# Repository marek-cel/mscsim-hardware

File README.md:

# mscsim-hardware
Flight simulator hardware.

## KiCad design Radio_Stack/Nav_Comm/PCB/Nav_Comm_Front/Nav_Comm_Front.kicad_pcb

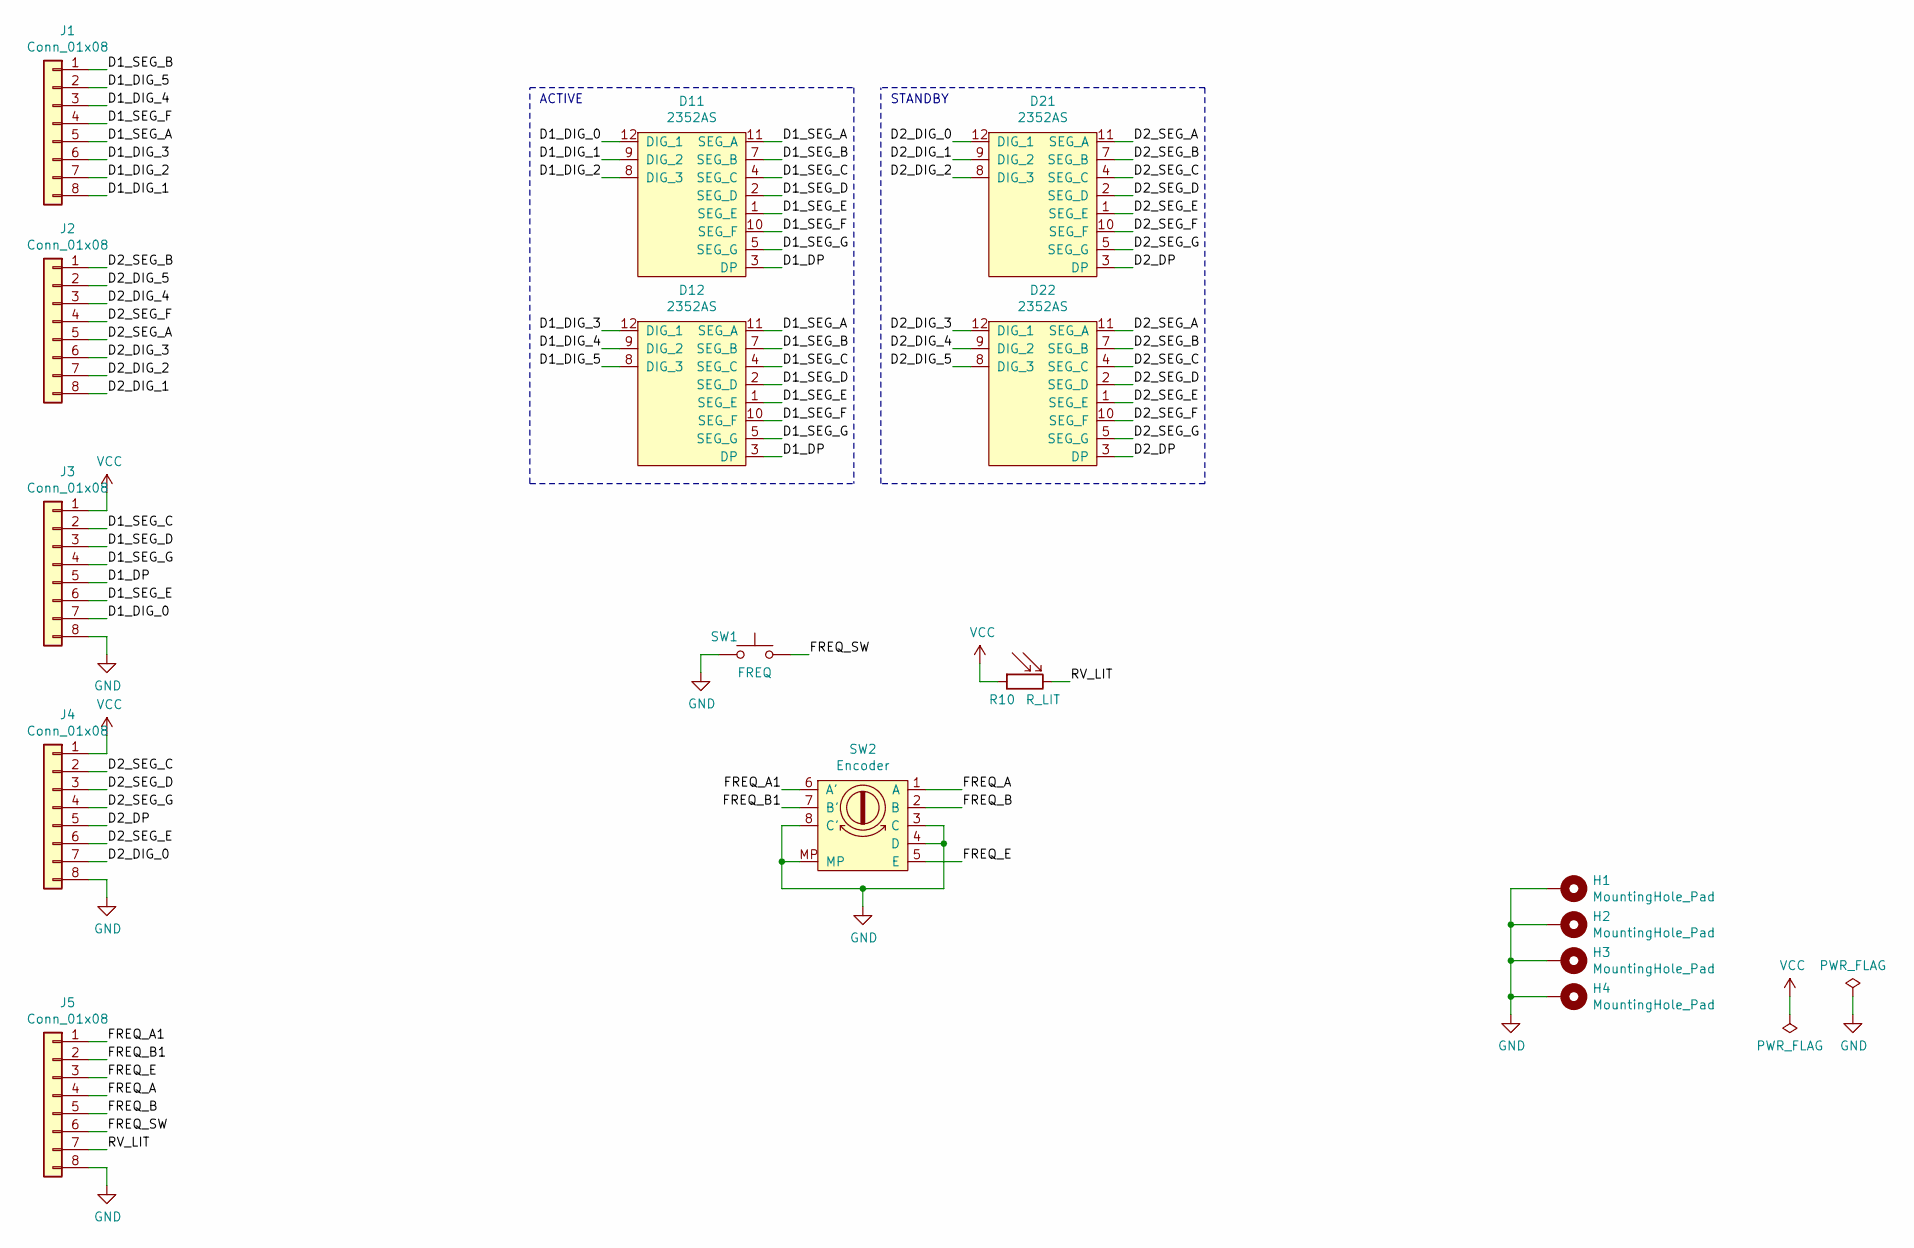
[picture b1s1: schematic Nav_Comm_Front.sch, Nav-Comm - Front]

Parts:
D11, D12, D21, D22: 2352AS
H1, H2, H3, H4: MountingHole_Pad; MountingHole_2.7mm_M2.5_Pad
J1, J2, J3, J4, J5: Conn_01x08; PinHeader_1x08_P2.54mm_Vertical
R10: R_LIT; GL55
SW1: FREQ; SW_PUSH_6mm
SW2: Encoder; EC11EBB24C03

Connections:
/D1_DIG_0: D11.12 (DIG_1), J3.7
/D1_DIG_1: D11.9 (DIG_2), J1.8
/D1_DIG_2: D11.8 (DIG_3), J1.7
/D1_DIG_3: D12.12 (DIG_1), J1.6
/D1_DIG_4: D12.9 (DIG_2), J1.3
/D1_DIG_5: D12.8 (DIG_3), J1.2
/D1_DP: D11.3 (DP), D12.3 (DP), J3.5
/D1_SEG_A: D11.11 (SEG_A), D12.11 (SEG_A), J1.5
/D1_SEG_B: D11.7 (SEG_B), D12.7 (SEG_B), J1.1
/D1_SEG_C: D11.4 (SEG_C), D12.4 (SEG_C), J3.2
/D1_SEG_D: D11.2 (SEG_D), D12.2 (SEG_D), J3.3
/D1_SEG_E: D11.1 (SEG_E), D12.1 (SEG_E), J3.6
/D1_SEG_F: D11.10 (SEG_F), D12.10 (SEG_F), J1.4
/D1_SEG_G: D11.5 (SEG_G), D12.5 (SEG_G), J3.4
/D2_DIG_0: D21.12 (DIG_1), J4.7
/D2_DIG_1: D21.9 (DIG_2), J2.8
/D2_DIG_2: D21.8 (DIG_3), J2.7
/D2_DIG_3: D22.12 (DIG_1), J2.6
/D2_DIG_4: D22.9 (DIG_2), J2.3
/D2_DIG_5: D22.8 (DIG_3), J2.2
/D2_DP: D21.3 (DP), D22.3 (DP), J4.5
/D2_SEG_A: D21.11 (SEG_A), D22.11 (SEG_A), J2.5
/D2_SEG_B: D21.7 (SEG_B), D22.7 (SEG_B), J2.1
/D2_SEG_C: D21.4 (SEG_C), D22.4 (SEG_C), J4.2
/D2_SEG_D: D21.2 (SEG_D), D22.2 (SEG_D), J4.3
/D2_SEG_E: D21.1 (SEG_E), D22.1 (SEG_E), J4.6
/D2_SEG_F: D21.10 (SEG_F), D22.10 (SEG_F), J2.4
/D2_SEG_G: D21.5 (SEG_G), D22.5 (SEG_G), J4.4
/FREQ_A: J5.4, SW2.1 (A)
/FREQ_A1: J5.1, SW2.6 (A')
/FREQ_B: J5.5, SW2.2 (B)
/FREQ_B1: J5.2, SW2.7 (B')
/FREQ_E: J5.3, SW2.5 (E)
/FREQ_SW: J5.6, SW1.1
/RV_LIT: J5.7, R10.2
GND: H1.1, H2.1, H3.1, H4.1, J3.8, J4.8, J5.8, SW1.2, SW2.3 (C), SW2.4 (D), SW2.8 (C'), SW2.MP
VCC: J3.1, J4.1, R10.1

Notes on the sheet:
ACTIVE
STANDBY

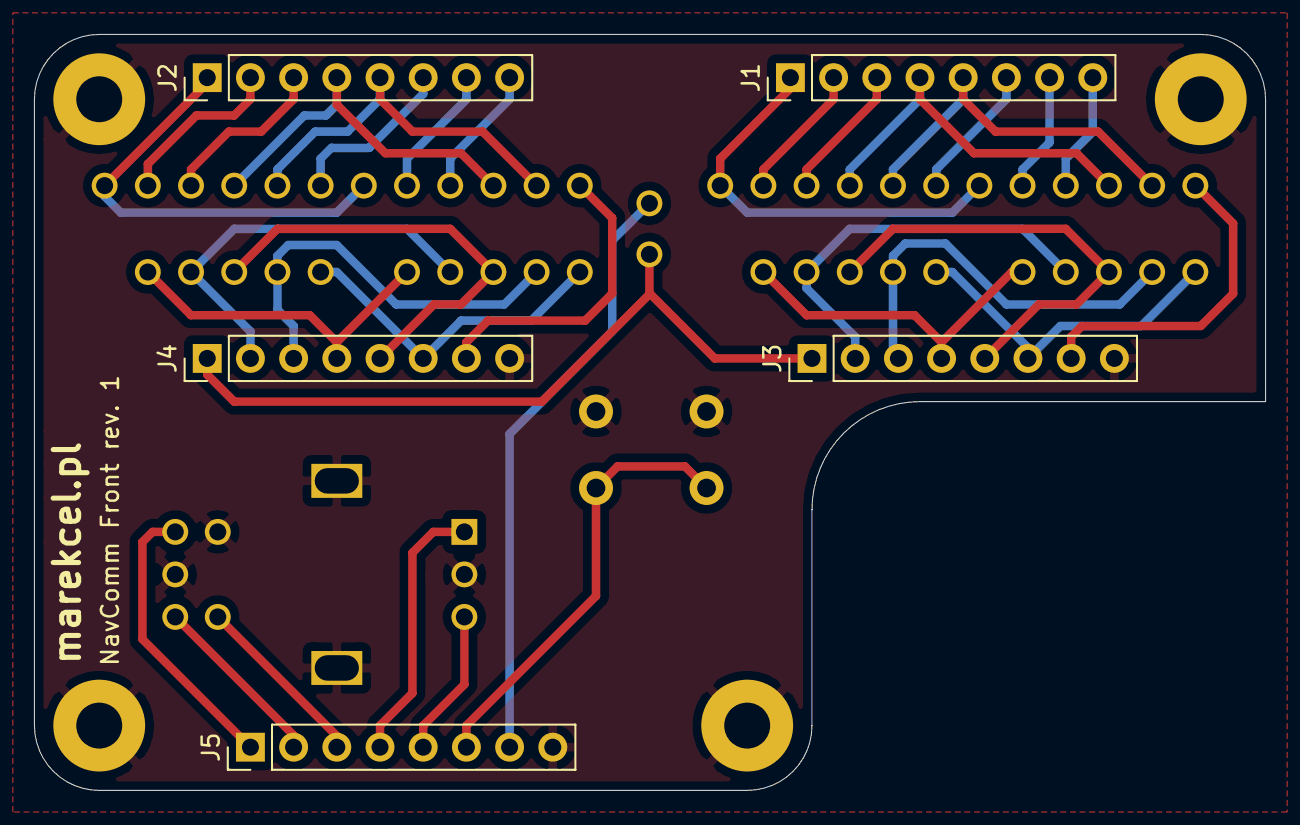
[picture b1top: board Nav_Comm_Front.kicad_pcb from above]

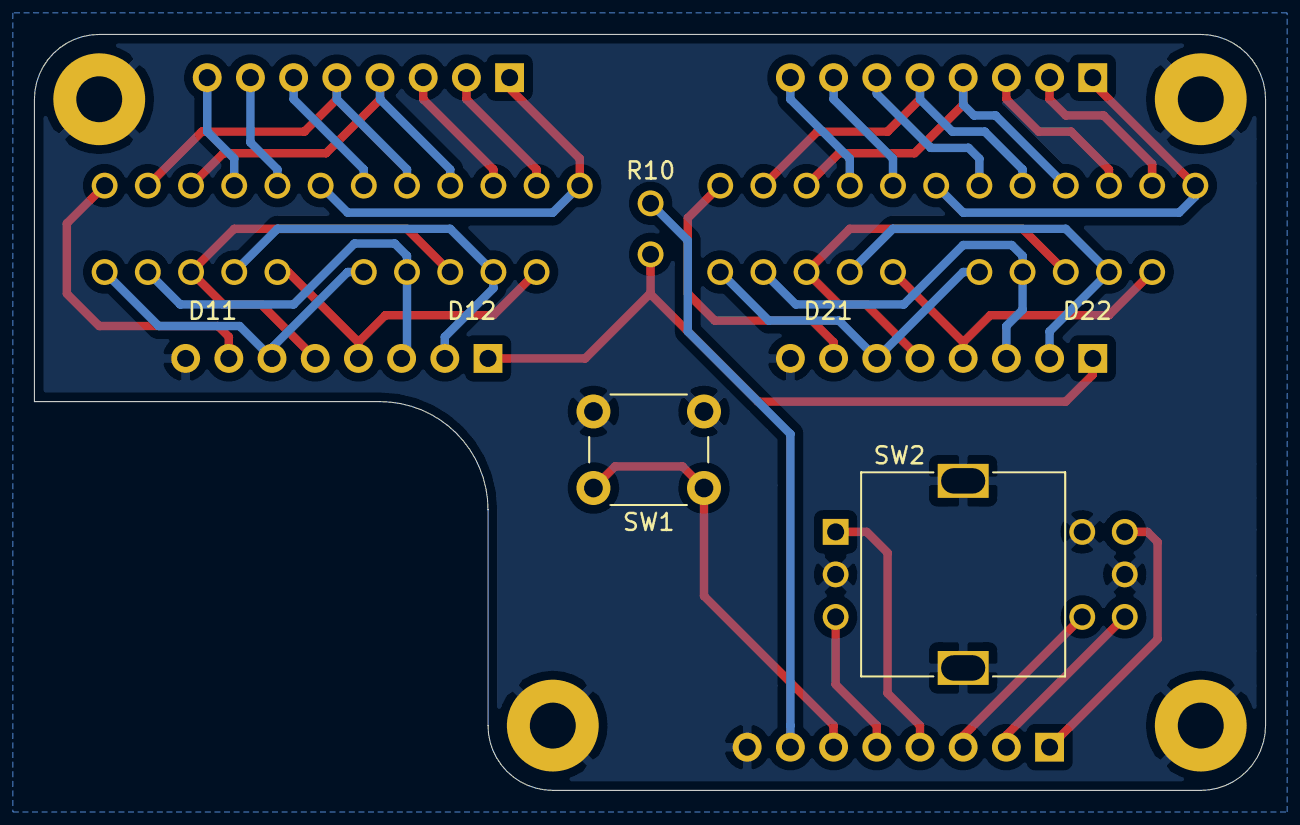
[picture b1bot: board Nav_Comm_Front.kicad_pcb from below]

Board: 2 copper layers, 72.4 x 44.5 mm, 16 parts (7 on the bottom side), 37 nets.

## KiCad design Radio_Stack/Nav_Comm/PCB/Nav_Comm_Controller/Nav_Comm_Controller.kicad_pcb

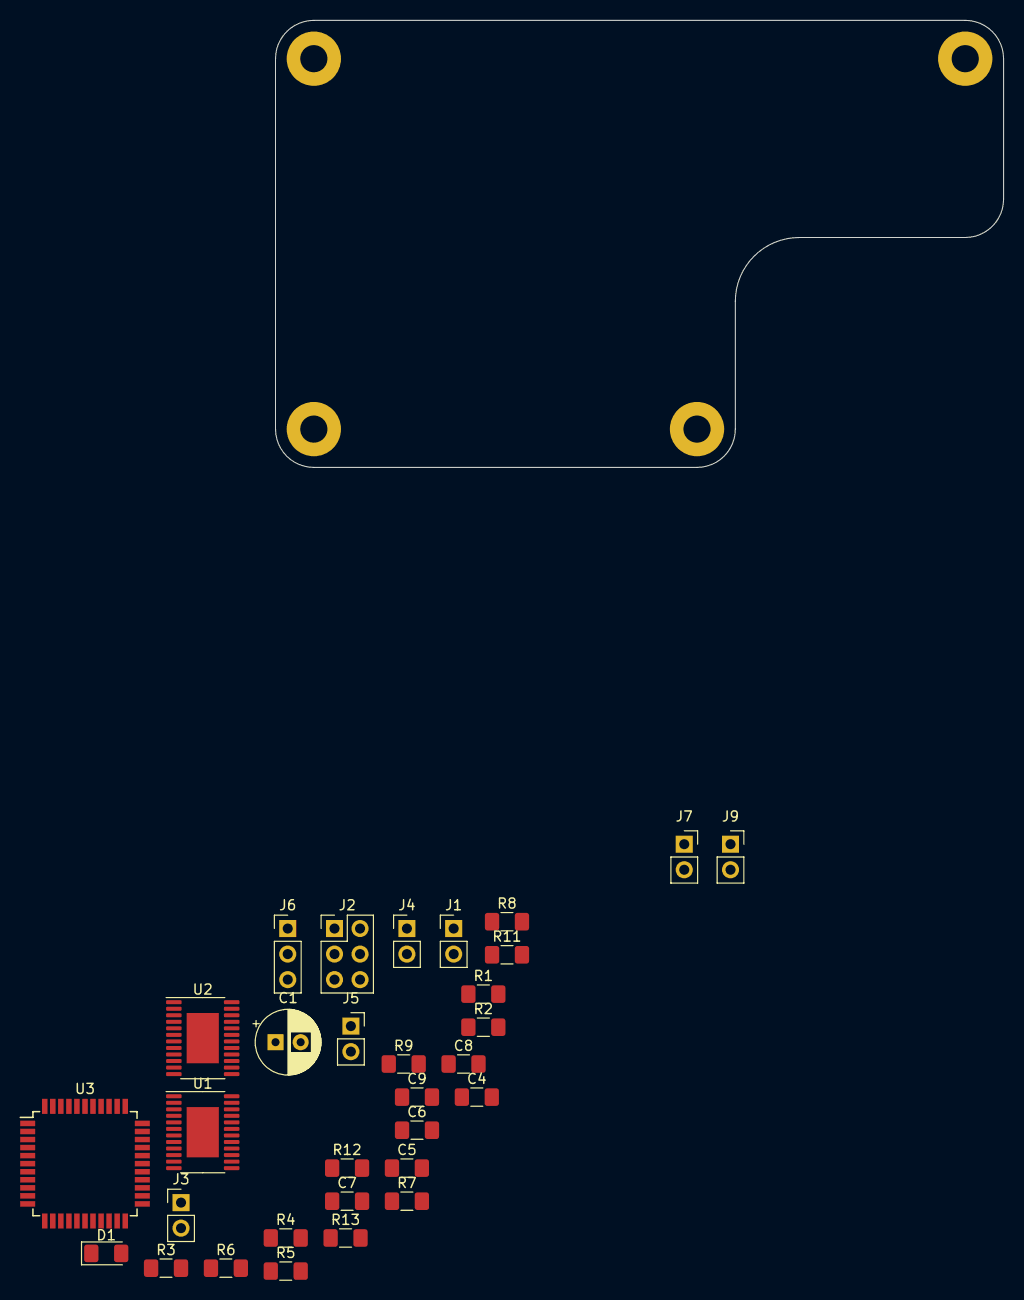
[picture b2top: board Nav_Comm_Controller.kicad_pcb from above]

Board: 2 copper layers, 72.4 x 44.5 mm, 35 parts (0 on the bottom side), 22 nets, no tracks yet.

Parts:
C1: 100uF; CP_Radial_D6.3mm_P2.50mm
C4, C5, C6, C7, C8, C9: 100n; C_1206_3216Metric_Pad1.42x1.75mm_HandSolder
D1: LED; LED_1206_3216Metric_Pad1.42x1.75mm_HandSolder
H1, H2, H3, H4: MountingHole_Pad; MountingHole_2.7mm_M2.5_Pad
J1: POWER; PinHeader_1x02_P2.54mm_Vertical
J2: ISP; PinHeader_2x03_P2.54mm_Vertical
J3: UART0; PinHeader_1x02_P2.54mm_Vertical
J4: UART1; PinHeader_1x02_P2.54mm_Vertical
J5: SW_PWR; PinSocket_1x02_P2.54mm_Vertical
J6: RV_VOL; PinHeader_1x03_P2.54mm_Vertical
J7: SW_FREQ; PinSocket_1x02_P2.54mm_Vertical
J9: RV_LIT; PinSocket_1x02_P2.54mm_Vertical
R1, R2, R3, R4, R5, R6, R7, R8, R9, R11, R12: 10k; R_1206_3216Metric_Pad1.42x1.75mm_HandSolder
R13: 200R; R_1206_3216Metric_Pad1.42x1.75mm_HandSolder
U1, U2: MAX7219; HTSSOP-24-1EP_4.4x7.8mm_P0.65mm_EP3.2x5mm
U3: ATmega324A-AU; TQFP-44_10x10mm_P0.8mm

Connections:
/A: C6.1, R6.2
/A1: C5.2, R5.2
/AV_LIT: J9.2, R11.2, U3.37
/AV_VOL: J6.2, U3.36
/B: C7.1, R7.2
/B1: C4.2, R4.2
/E: C8.1, R8.2
/MISO: J2.1, U3.2
/MOSI: J2.4, U3.1
/RESET: J2.5, R3.1, U3.4
/RXD0: J3.1, U3.9
/RXD1: J4.1, U3.11
/SCK: J2.3, U3.3
/SW_FREQ: C9.2, J7.1, R9.1
/SW_PWR: J5.1, R12.2
/TXD0: J3.2, U3.10
/TXD1: J4.2, U3.12
GND: C1.2, C4.1, C5.1, C6.2, C7.2, C8.2, C9.1, D1.1, H1.1, H2.1, H3.1, H4.1, J1.2, J2.6, J5.2, J6.3, J7.2, R11.1, U1.4, U1.9, U2.4, U2.9, U3.6, U3.18, U3.28, U3.39
unnamed: D1.2, R13.1
unnamed: R1.1, U1.18
unnamed: R2.1, U2.18
VCC: C1.1, J1.1, J2.2, J6.1, J9.1, R1.2, R2.2, R3.2, R4.1, R5.1, R6.1, R7.1, R8.1, R9.2, R12.1, R13.2, U1.19, U2.19, U3.5, U3.17, U3.38

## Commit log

2020-07-19 custom electronic components KiCAD symbols
2020-07-19 custom electronic components KiCAD footprints
2020-07-19 custom electronic components 3D models
2020-07-19 Nav-Comm module frequency knobs 3D models
2020-07-19 Nav-Comm module PCB's
2020-07-19 custom electronic components 3D models, Nav-Comm module PCB's
2020-07-19 custom electronic components KiCAD symbols, custom electronic components KiCAD footprints, Nav-Comm module PCB's
